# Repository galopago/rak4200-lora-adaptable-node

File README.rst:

=======================================================================================================================================
RAK4200 based LoRa node, with multiple expansion possibilities and designed to fit inside a generic 83x58x33mm waterproof enclosure box.
=======================================================================================================================================

LoRa node powered by AA batteries ready to install inside an easy to find waterproof enclosure.

Read this in other languages: `Español </docs/README.es.rst>`_

.. image:: /docs/pcb3d.png

Key features:
-------------
* Powered by 2xAA (1.5v) batteries or a single (3.0v) battery.
* Waterproof if installed in an "easy to find worldwide" 83x58x33mm waterproof plastic enclosure (multiple choices: clear cover, wall mounting tabs, etc.).
* Class A battery powered or Class C external powered via screw terminal.
* RAK4200 = SX1276+STM32L071. So no additional cpu/microcontroller needed for a complete solution.
* Can be programmed using `RAK Unified Interface (RUI) API, <https://doc.rakwireless.com/quick-start/rak5010-wistrio-nb-iot-tracker/rui-online-compiler>`_ for rapid development or STM32 CUBE LoRa stack.
* TH pad for a spring antenna or U.FL connector for external antenna.
* Prototyping/expansion area.

How to use this repository
--------------------------

The PCB was developed in KiCad V5.1, and include some elements from the official repo.

To setup KiCad to use the downloaded library from the repo instead of the stock that came with the installer, `this post <https://forum.kicad.info/t/library-management-in-kicad-version-5/14636>`_ will give you some lights.

Directory structure
-------------------
* The root folder contains KiCad files: project, schematic and PCB.
* library directory (git submodule) contains schematics symbol libraries.
* modules directory (git submodule) contains footprint libraries.
* packages3d directory (git submodule) contains 3D model libraries.
* gerber/single directory contains ready to manufacture files, for a single board.
* gerber/panel_100mmx100mm directory contains ready to manufacture files that fits in a 100mm x 100mm panel (use Vcuts!).

License
-------

.. image:: https://i.creativecommons.org/l/by/4.0/88x31.png
   :target: http://creativecommons.org/licenses/by/4.0/

This is an Open Hardware project and is licensed under a `Creative Commons Attribution 4.0 International License, <http://creativecommons.org/licenses/by/4.0/>`_

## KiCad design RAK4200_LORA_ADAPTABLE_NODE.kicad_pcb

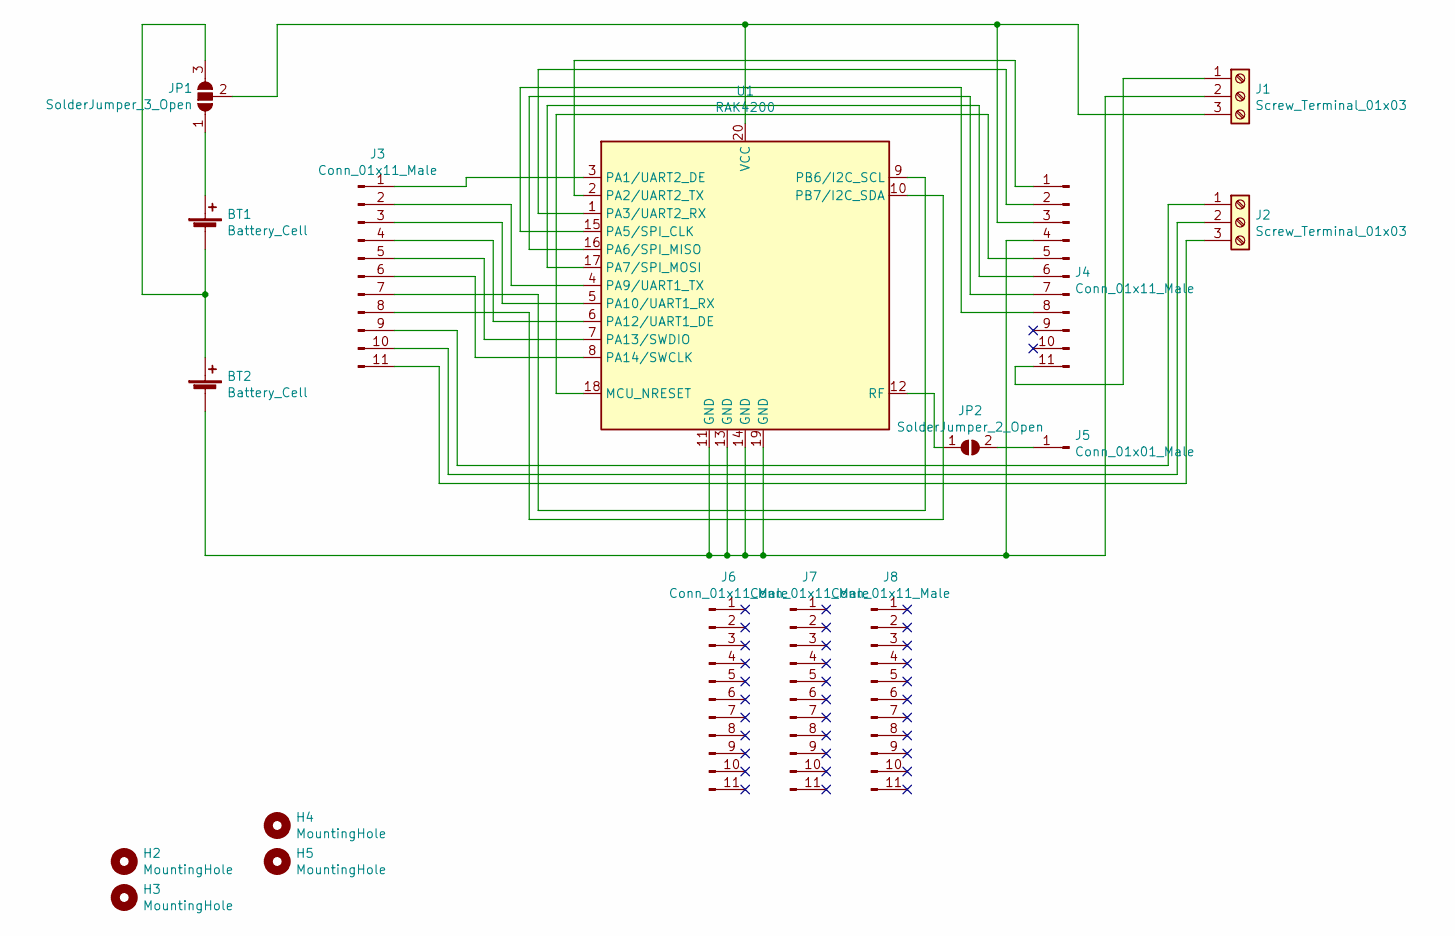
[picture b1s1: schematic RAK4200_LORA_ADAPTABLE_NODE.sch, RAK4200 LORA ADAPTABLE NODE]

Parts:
BT1, BT2: Battery_Cell; BatteryHolder_Keystone_2460_1xAA
H2, H3, H4, H5: MountingHole; MountingHole_3mm
J1, J2: Screw_Terminal_01x03; TerminalBlock_4Ucon_1x03_P3.50mm_Horizontal
J3, J4, J6, J7, J8: Conn_01x11_Male; PinHeader_1x11_P2.54mm_Vertical
J5: Conn_01x01_Male; PinHeader_1x01_P2.54mm_Vertical
JP1: SolderJumper_3_Open; SolderJumper-3_P1.3mm_Open_RoundedPad1.0x1.5mm_NumberLabels
JP2: SolderJumper_2_Open; SolderJumper-2_P1.3mm_Open_RoundedPad1.0x1.5mm
U1: RAK4200

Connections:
unnamed: BT1.1 (+), JP1.1 (A)
unnamed: BT1.2 (-), BT2.1 (+), JP1.3 (B)
unnamed: BT2.2 (-), J1.2, J4.4, U1.11 (GND), U1.13 (GND), U1.14 (GND), U1.19 (GND)
unnamed: J1.1, J4.11
unnamed: J1.3, J4.3, JP1.2 (C), U1.20 (VCC)
unnamed: J2.1, J3.9
unnamed: J2.2, J3.10
unnamed: J2.3, J3.11
unnamed: J3.1, U1.3 (PA1/UART2_DE)
unnamed: J3.2, U1.4 (PA9/UART1_TX)
unnamed: J3.3, U1.5 (PA10/UART1_RX)
unnamed: J3.4, U1.6 (PA12/UART1_DE)
unnamed: J3.5, U1.7 (PA13/SWDIO)
unnamed: J3.6, U1.8 (PA14/SWCLK)
unnamed: J3.7, U1.9 (PB6/I2C_SCL)
unnamed: J3.8, U1.10 (PB7/I2C_SDA)
unnamed: J4.1, U1.2 (PA2/UART2_TX)
unnamed: J4.2, U1.1 (PA3/UART2_RX)
unnamed: J4.5, U1.18 (MCU_NRESET)
unnamed: J4.6, U1.17 (PA7/SPI_MOSI)
unnamed: J4.7, U1.16 (PA6/SPI_MISO)
unnamed: J4.8, U1.15 (PA5/SPI_CLK)
unnamed: J5.1, JP2.2 (B)
unnamed: JP2.1 (A), U1.12 (RF)

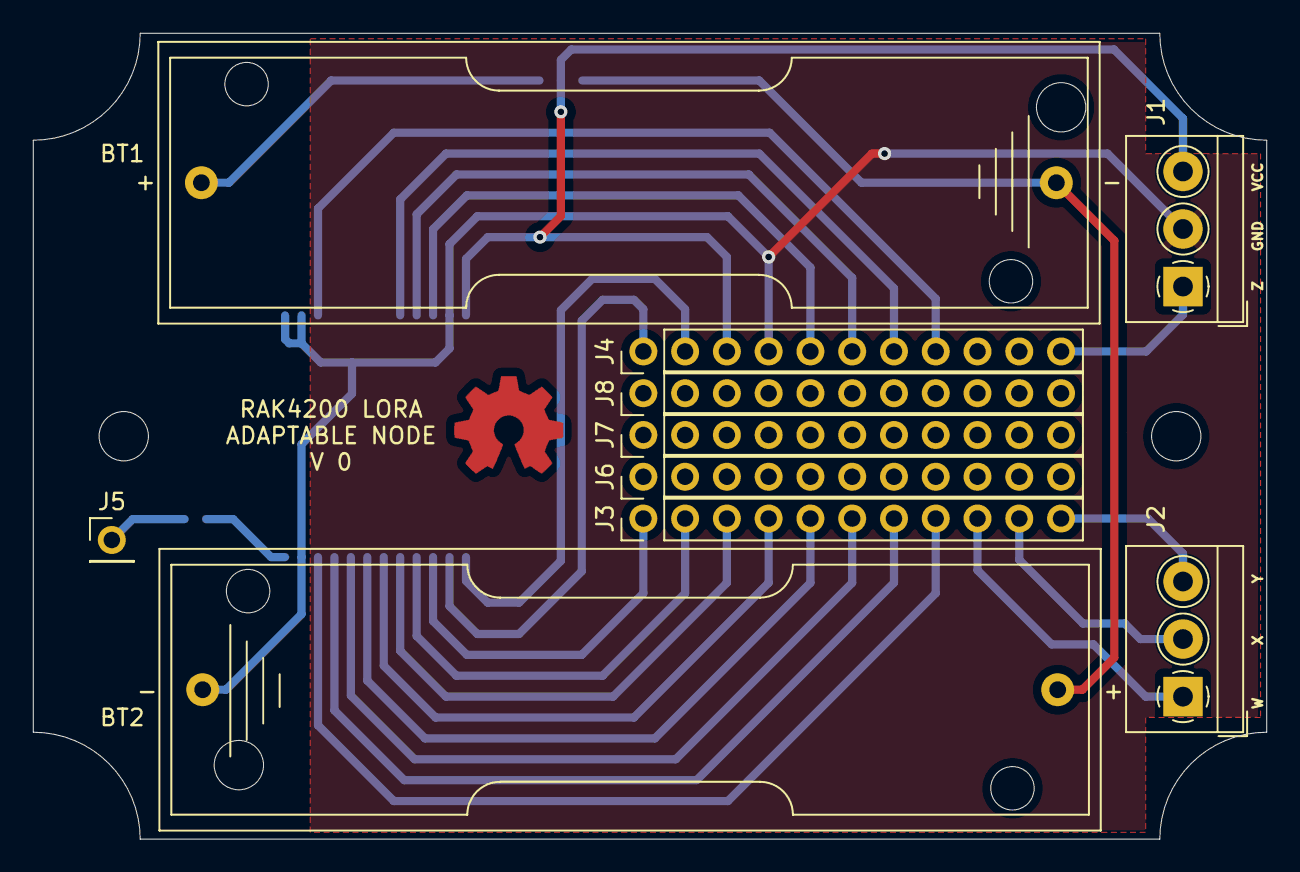
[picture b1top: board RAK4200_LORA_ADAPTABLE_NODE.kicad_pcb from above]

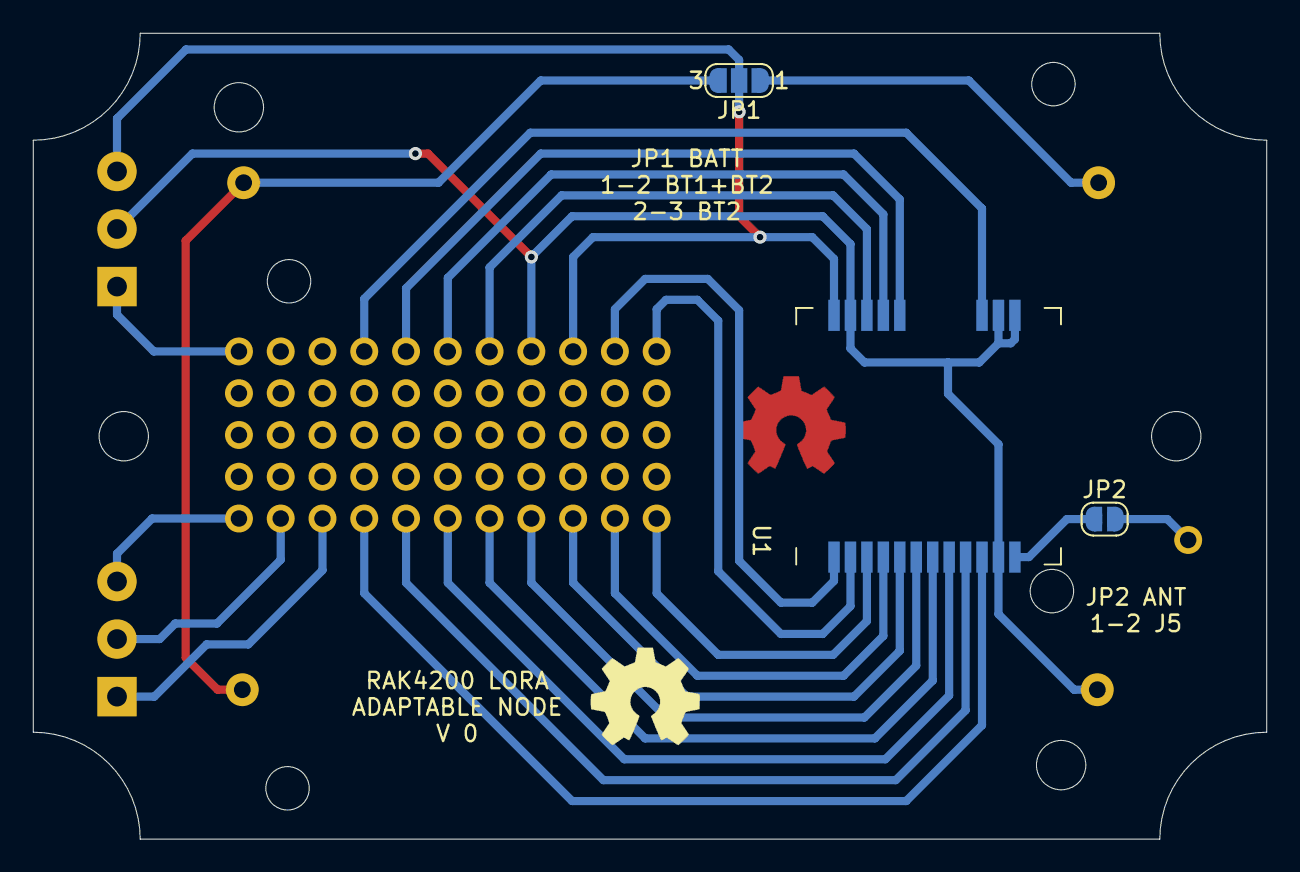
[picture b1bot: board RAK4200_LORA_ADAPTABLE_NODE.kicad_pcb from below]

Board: 2 copper layers, 75.0 x 49.0 mm, 17 parts (3 on the bottom side), 24 nets.

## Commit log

2020-07-23 battery holder, solder jumper and screw terminal added
2020-07-24 expansion connectors added
2020-07-24 all I/O already connected
2020-07-25 all traces routed
2020-07-25 all silks msg done
2020-07-25 copper plane - single board gerbers
2020-07-25 100mmx100mm panel gerbers
2020-07-28 removed misnamed submodules
2020-07-28 removed misnamed submodules again :s
2020-07-28 added reference to library and modules submodules
2020-07-28 removed library submodule
2020-07-28 add library submodule
2020-07-30 all submodules links added
2020-07-30 info files added, English and Spanish
2020-07-30 renamed pcb png file
2020-08-18 added pcb pinout info to docs folder
2020-08-18 silkscreen ext ant fix
2020-09-21 removed packages3d modules
2020-09-21 removed modules modules
2020-09-21 removed library modules
2020-09-21 removed text about submodules
2020-09-21 removed text about submodules in spanish readme
